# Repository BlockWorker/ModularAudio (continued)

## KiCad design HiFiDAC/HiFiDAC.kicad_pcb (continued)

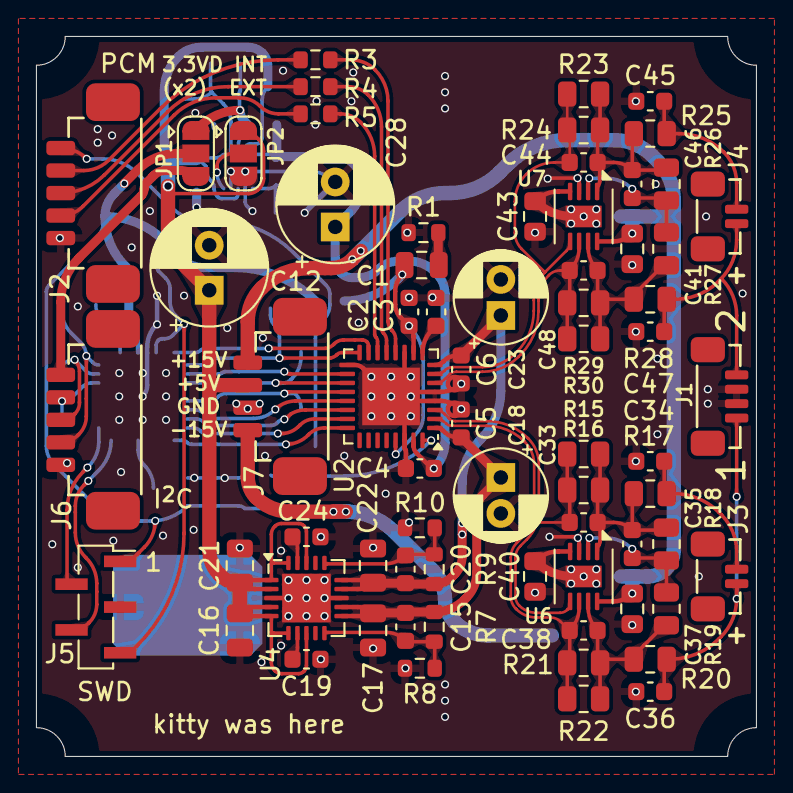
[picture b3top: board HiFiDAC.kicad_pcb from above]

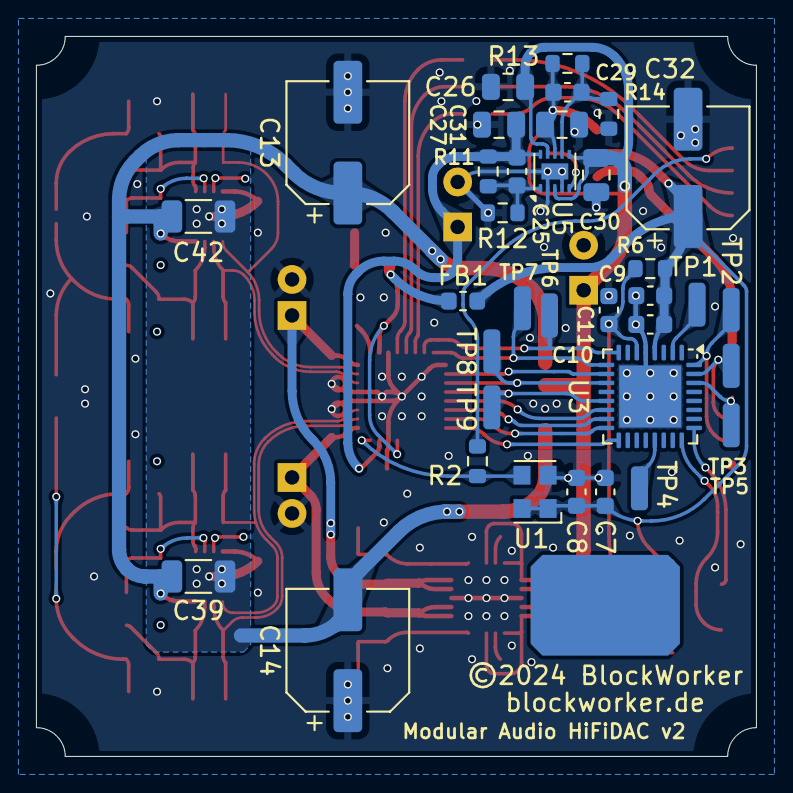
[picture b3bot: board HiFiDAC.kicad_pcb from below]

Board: 4 copper layers, 40.0 x 40.0 mm, 104 parts (35 on the bottom side), 59 nets.

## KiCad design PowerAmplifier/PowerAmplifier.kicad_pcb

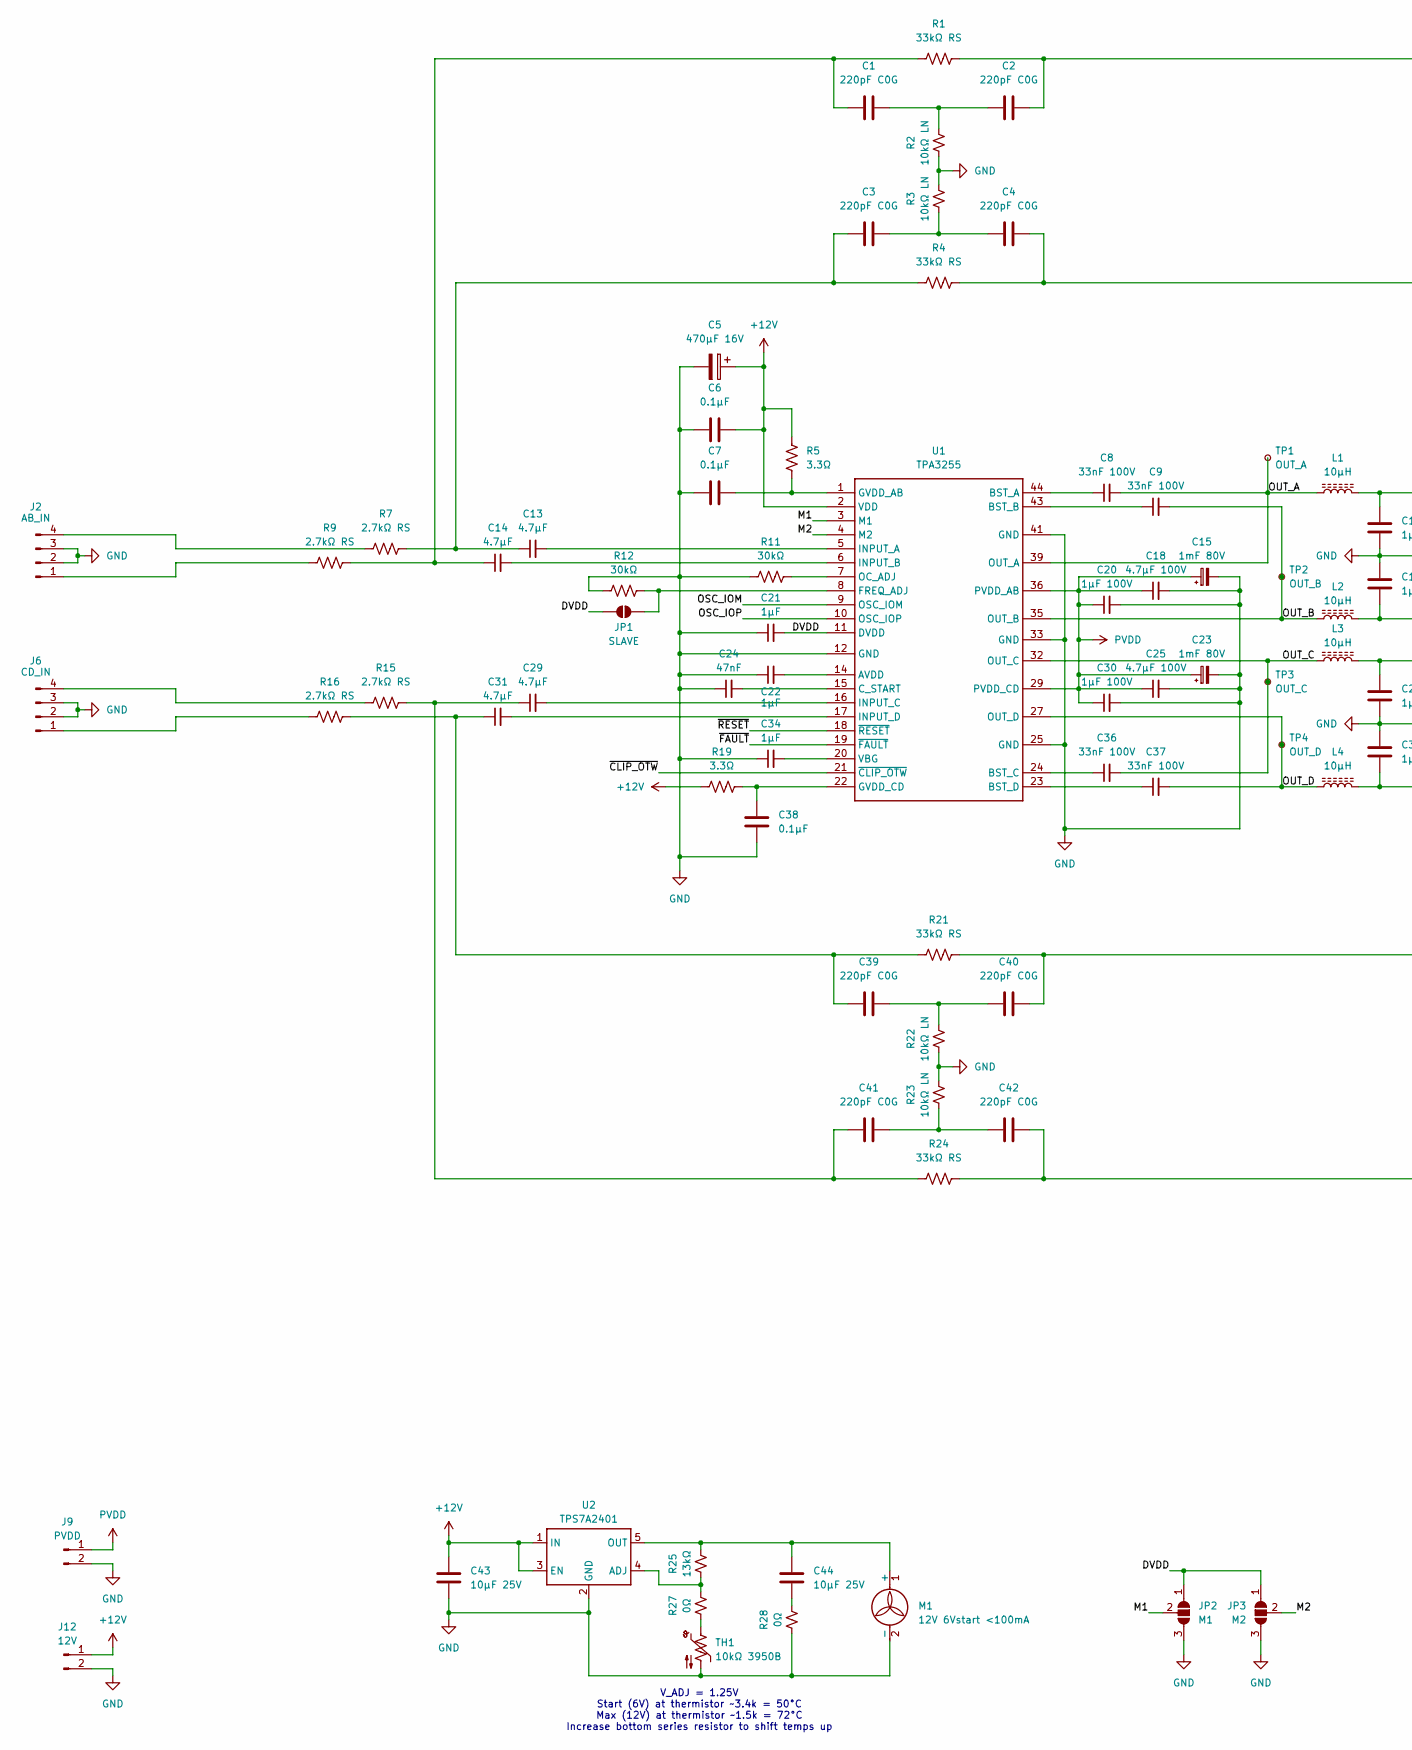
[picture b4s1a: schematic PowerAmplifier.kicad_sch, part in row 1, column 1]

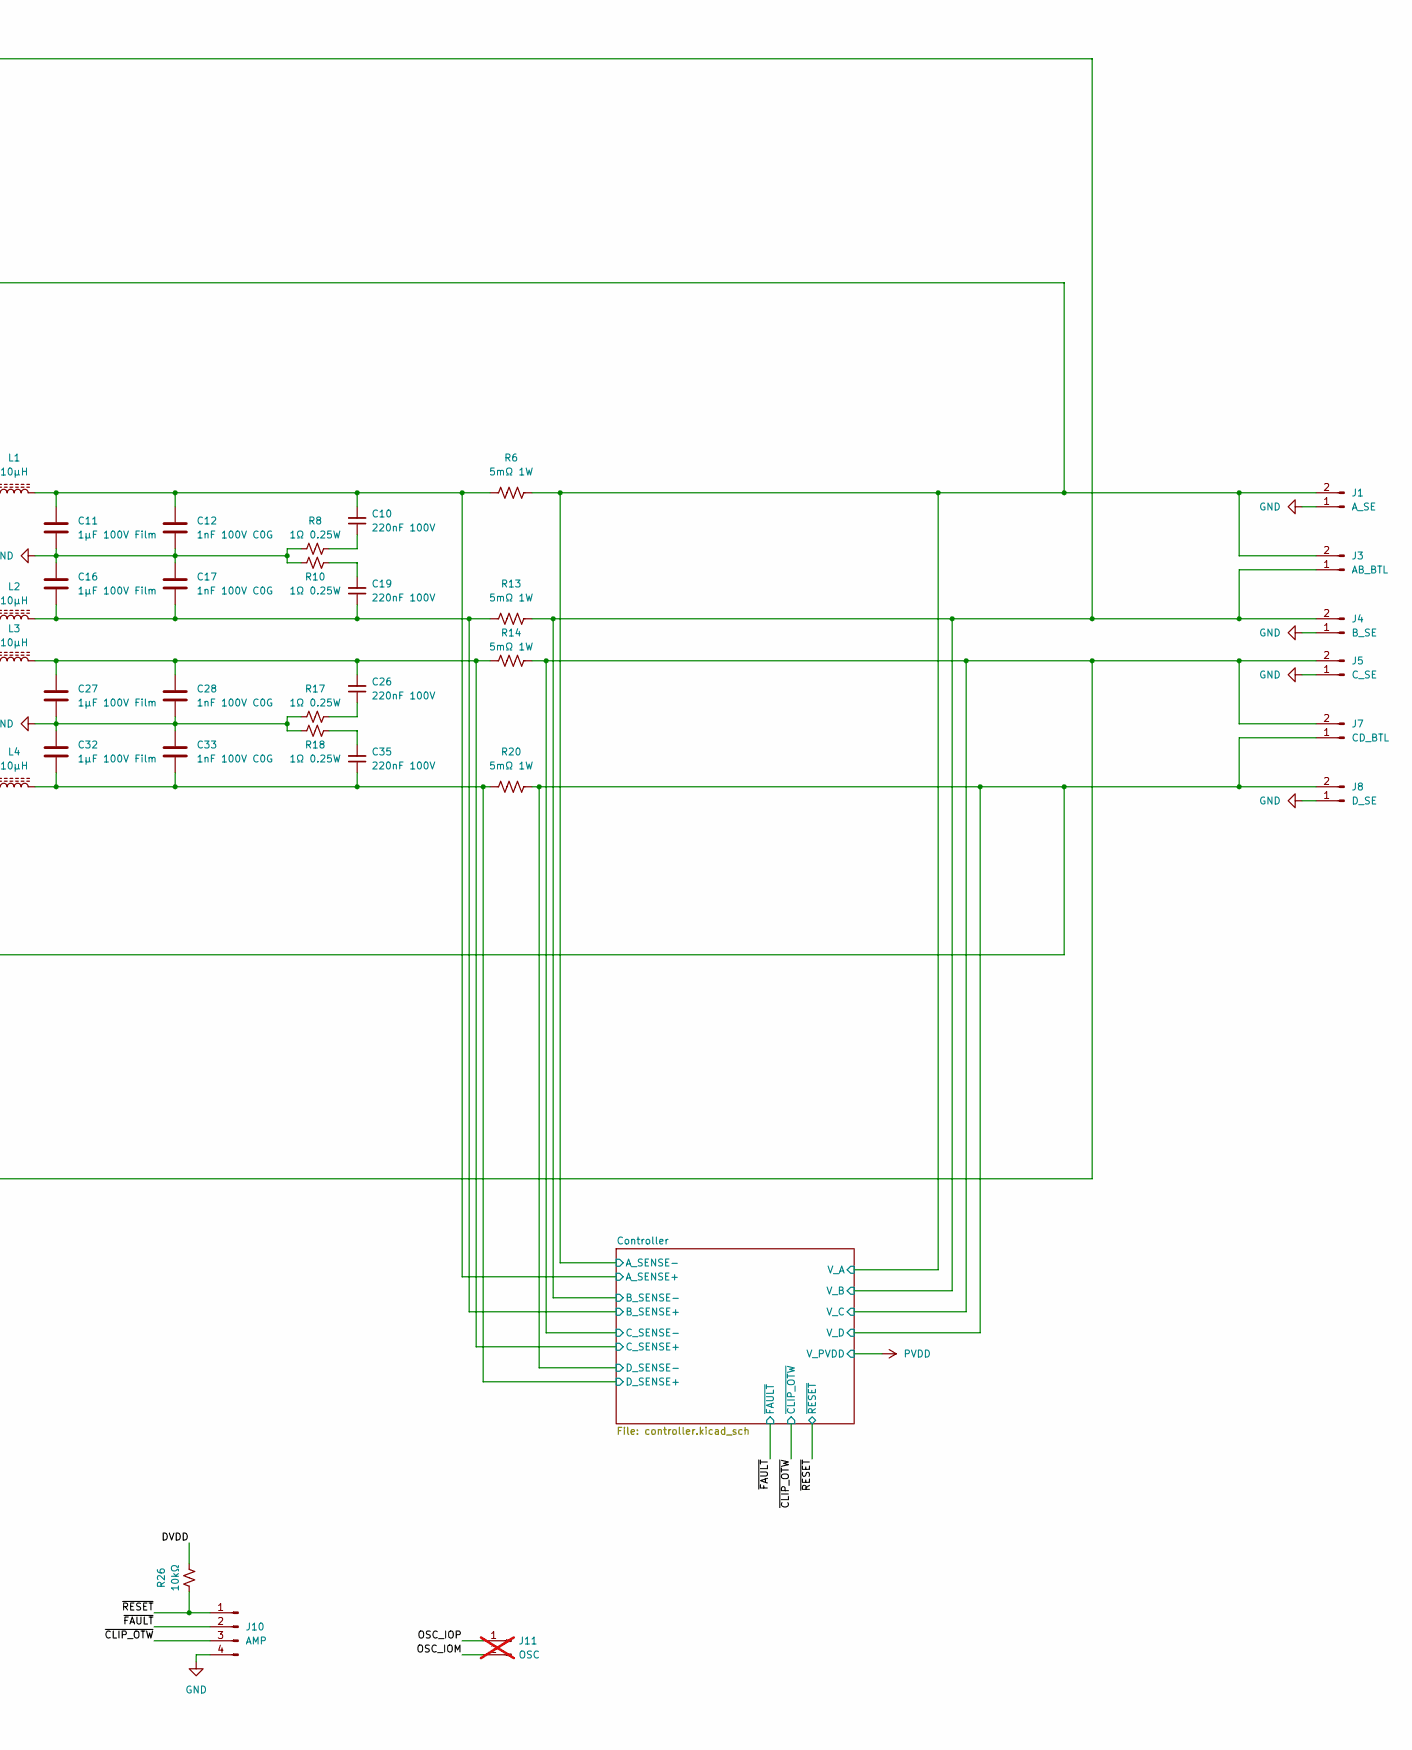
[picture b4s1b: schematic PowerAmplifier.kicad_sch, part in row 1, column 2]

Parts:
C1, C2, C3, C4, C39, C40, C41, C42: 220pF C0G; C_0603_1608Metric
C5: 470µF 16V; CP_Radial_D8.0mm_P3.50mm
C6, C7, C38: 0.1µF; C_0603_1608Metric
C8, C9, C36, C37: 33nF 100V; C_0603_1608Metric
C10, C19, C26, C35: 220nF 100V; C_0805_2012Metric
C11, C16, C27, C32: 1µF 100V Film; C_Rect_L7.0mm_W6.0mm_P5.00mm
C12, C17, C28, C33: 1nF 100V C0G; C_0603_1608Metric
C13, C14, C29, C31: 4.7µF; C_Rect_L7.2mm_W7.2mm_P5.00mm_FKS2_FKP2_MKS2_MKP2
C15, C23: 1mF 80V; CP_Radial_D16.0mm_P7.50mm
C18, C25: 4.7µF 100V; C_1206_3216Metric
C20, C30: 1µF 100V; C_1206_3216Metric
C21, C22, C34: 1µF; C_0603_1608Metric
C24: 47nF; C_0603_1608Metric
C43, C44: 10µF 25V; C_0805_2012Metric
J1: A_SE; TE_MATE-N-LOK_1-770872-x_1x02_P4.14mm_Vertical
J2: AB_IN; Amphenol_MINITEK_0.8_4P_V_BoardEdge
J3: AB_BTL; TE_MATE-N-LOK_1-770872-x_1x02_P4.14mm_Vertical
J4: B_SE; TE_MATE-N-LOK_1-770872-x_1x02_P4.14mm_Vertical
J5: C_SE; TE_MATE-N-LOK_1-770872-x_1x02_P4.14mm_Vertical
J6: CD_IN; Amphenol_MINITEK_0.8_4P_V_BoardEdge
J7: CD_BTL; TE_MATE-N-LOK_1-770872-x_1x02_P4.14mm_Vertical
J8: D_SE; TE_MATE-N-LOK_1-770872-x_1x02_P4.14mm_Vertical
J9: PVDD; TE_644749-2
J10: AMP; Amphenol_MINITEK_0.8_4P_V_BoardEdge
J11: OSC; Amphenol_MINITEK_0.8_2P_V; not fitted
J12: 12V; Amphenol_MINITEK_0.8_2P_V_BoardEdge
JP1: SLAVE; SolderJumper-2_P1.3mm_Open_RoundedPad1.0x1.5mm
JP2: M1; SolderJumper-3_P1.3mm_Open_RoundedPad1.0x1.5mm
JP3: M2; SolderJumper-3_P1.3mm_Open_RoundedPad1.0x1.5mm
L1, L2, L3, L4: 10µH; L_ICE_1D17A
M1: 12V 6Vstart <100mA; Amphenol_MINITEK_0.8_2P_V
R1, R4, R21, R24: 33kΩ RS; R_0805_2012Metric
R2, R3, R22, R23: 10kΩ LN; R_0603_1608Metric
R5, R19: 3.3Ω; R_0805_2012Metric
R6, R13, R14, R20: 5mΩ 1W; R_0612_1632Metric
R7, R9, R15, R16: 2.7kΩ RS; R_0805_2012Metric
R8, R10, R17, R18: 1Ω 0.25W; R_0603_1608Metric
R11, R12: 30kΩ; R_0603_1608Metric
R25: 13kΩ; R_0603_1608Metric
R26: 10kΩ; R_0603_1608Metric
R27, R28: 0Ω; R_0603_1608Metric
TH1: 10kΩ 3950B; R_0603_1608Metric
TP1: OUT_A; TP_0603_1608Metric_Fused
TP2: OUT_B; TP_0603_1608Metric_Fused
TP3: OUT_C; TP_0603_1608Metric_Fused
TP4: OUT_D; TP_0603_1608Metric_Fused
U1: TPA3255; HTSSOP-44_6.1x14mm_P0.635mm
U2: TPS7A2401; SOT-23-5

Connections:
+12V: C5.1, C6.1, C43.1, J12.1, R5.2, R19.1, U1.2 (VDD), U2.1 (IN), U2.3 (EN); also elsewhere on the board
/Controller/A_SENSE+: C10.2, C11.1, C12.1, L1.2, R6.2; also elsewhere on the board
/Controller/A_SENSE-: C4.1, J1.2, J3.2, R4.1, R6.1; also elsewhere on the board
/Controller/B_SENSE+: C16.2, C17.2, C19.1, L2.2, R13.2; also elsewhere on the board
/Controller/B_SENSE-: C2.1, J3.1, J4.2, R1.1, R13.1; also elsewhere on the board
/Controller/C_SENSE+: C26.2, C27.1, C28.1, L3.2, R14.2; also elsewhere on the board
/Controller/C_SENSE-: C42.1, J5.2, J7.2, R14.1, R24.1; also elsewhere on the board
/Controller/D_SENSE+: C32.2, C33.2, C35.1, L4.2, R20.2; also elsewhere on the board
/Controller/D_SENSE-: C40.1, J7.1, J8.2, R20.1, R21.1; also elsewhere on the board
/DVDD: C21.2, JP1.1 (A), JP2.1 (A), JP3.1 (A), R26.1, U1.11 (DVDD)
/M1: JP2.2 (C), U1.3 (M1)
/M2: JP3.2 (C), U1.4 (M2)
/OSC_IOM: J11.2, U1.9 (OSC_IOM)
/OSC_IOP: J11.1, U1.10 (OSC_IOP)
/OUT_A: C8.2, L1.1, TP1.1, U1.39 (OUT_A), U1.40 (OUT_A)
/OUT_B: C9.2, L2.1, TP2.1, U1.35 (OUT_B)
/OUT_C: C36.2, L3.1, TP3.1, U1.32 (OUT_C)
/OUT_D: C37.2, L4.1, TP4.1, U1.27 (OUT_D), U1.28 (OUT_D)
/~CLIP_OTW: J10.3, U1.21 (~CLIP_OTW); also elsewhere on the board
/~FAULT: J10.2, U1.19 (~FAULT); also elsewhere on the board
/~RESET: J10.1, R26.2, U1.18 (~RESET); also elsewhere on the board
GND: C5.2, C6.2, C7.2, C11.2, C12.2, C15.2, C16.1, C17.1, C18.2, C20.2, C21.1, C22.1, C23.2, C24.1, C25.2, C27.2, C28.2, C30.2, C32.1, C33.1, C34.1, C38.2, C43.2, J1.1, J2.2, J2.3, J4.1, J5.1, J6.2, J6.3, J8.1, J9.2, J10.4, J12.2, JP2.3 (B), JP3.3 (B), M1.2 (-), R2.2, R3.1, R8.2, R10.2, R11.2, R12.2, R17.2, R18.2, R22.2, R23.1, R28.2, TH1.2, U1.12 (GND), U1.13 (GND), U1.25 (GND), U1.26 (GND), U1.33 (GND), U1.34 (GND), U1.41 (GND), U1.42 (GND), U2.2 (GND); also elsewhere on the board
unnamed: C1.1, C2.2, R2.1
unnamed: C1.2, C14.1, R1.2, R9.1
unnamed: C3.1, C4.2, R3.2
unnamed: C10.1, R8.1
unnamed: C3.2, C13.1, R4.2, R7.1
unnamed: C19.2, R10.1
unnamed: C26.1, R17.1
unnamed: C29.1, C41.2, R15.1, R24.2
unnamed: C31.1, C39.2, R16.1, R21.2
unnamed: C35.2, R18.1
unnamed: C39.1, C40.2, R22.1
unnamed: C41.1, C42.2, R23.2
unnamed: C44.2, R28.1
unnamed: J2.1, R9.2
unnamed: J2.4, R7.2
unnamed: J6.1, R16.2
unnamed: J6.4, R15.2
unnamed: JP1.2 (B), R12.1, U1.8 (FREQ_ADJ)
unnamed: C44.1, M1.1 (+), R25.1, U2.5 (OUT)
unnamed: R27.2, TH1.1
unnamed: C22.2, U1.14 (AVDD)
unnamed: C8.1, U1.44 (BST_A)
unnamed: C9.1, U1.43 (BST_B)
unnamed: C36.1, U1.24 (BST_C)
unnamed: C37.1, U1.23 (BST_D)
unnamed: C24.2, U1.15 (C_START)
unnamed: C7.1, R5.1, U1.1 (GVDD_AB)
unnamed: C38.1, R19.2, U1.22 (GVDD_CD)
unnamed: C13.2, U1.5 (INPUT_A)
unnamed: C14.2, U1.6 (INPUT_B)
unnamed: C29.2, U1.16 (INPUT_C)
unnamed: C31.2, U1.17 (INPUT_D)
unnamed: R11.1, U1.7 (OC_ADJ)
unnamed: C34.2, U1.20 (VBG)
unnamed: R25.2, R27.1, U2.4 (ADJ)
PVDD: C15.1, C18.1, C20.1, C23.1, C25.1, C30.1, J9.1, U1.29 (PVDD_CD), U1.30 (PVDD_CD), U1.31 (PVDD_CD), U1.36 (PVDD_AB), U1.37 (PVDD_AB), U1.38 (PVDD_AB); also elsewhere on the board

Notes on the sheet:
V_ADJ = 1.25V Start (6V) at thermistor ~3.4k = 50°C Max (12V) at thermistor ~1.5k = 72°C Increase bottom series resistor to shift temps up

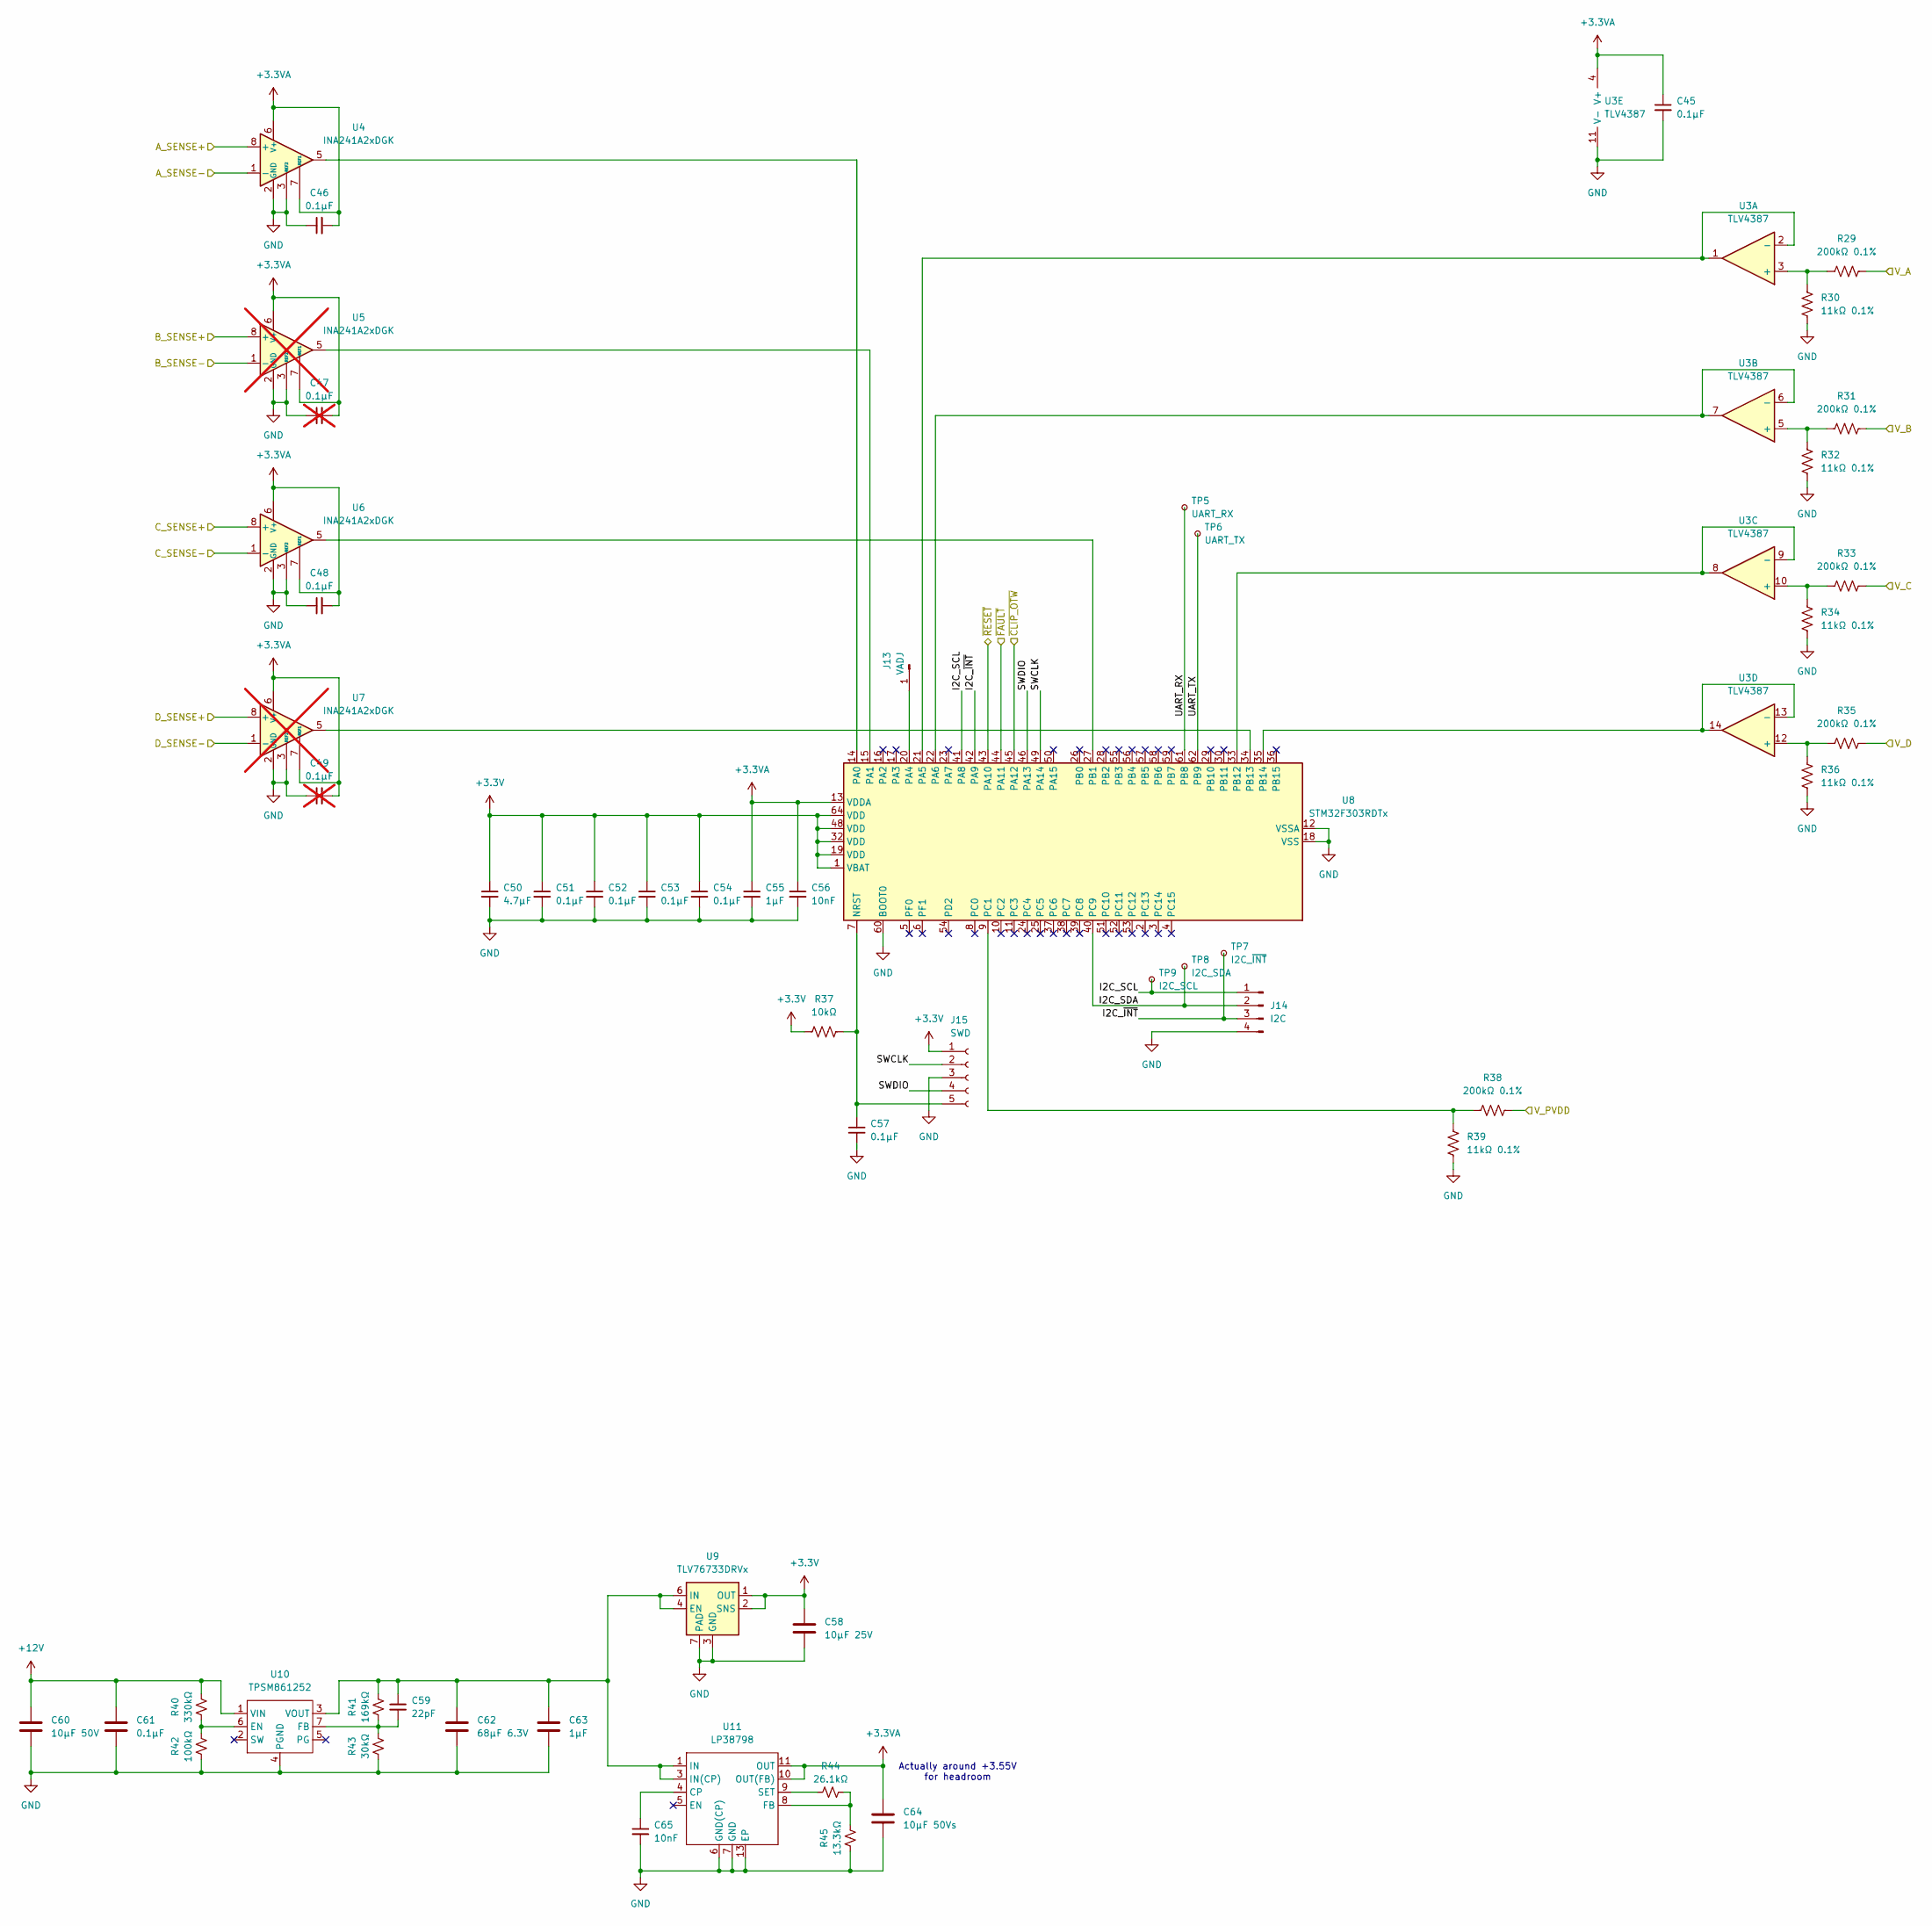
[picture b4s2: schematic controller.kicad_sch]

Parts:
C45, C46, C48, C51, C52, C53, C54, C57, C61: 0.1µF; C_0603_1608Metric
C47, C49: 0.1µF; C_0603_1608Metric; not fitted
C50: 4.7µF; C_0603_1608Metric
C55, C63: 1µF; C_0603_1608Metric
C56, C65: 10nF; C_0603_1608Metric
C58: 10µF 25V; C_0805_2012Metric
C59: 22pF; C_0603_1608Metric
C60: 10µF 50V; C_1206_3216Metric
C62: 68µF 6.3V; C_1206_3216Metric
C64: 10µF 50Vs; C_0805_2012Metric
J13: VADJ; PinHeader_1x01_P2.54mm_Vertical
J14: I2C; Amphenol_MINITEK_0.8_4P_V_BoardEdge
J15: SWD; PinSocket_1x05_P1.27mm_Vertical_SMD_Pin1Right
R29, R31, R33, R35, R38: 200kΩ 0.1%; R_0603_1608Metric
R30, R32, R34, R36, R39: 11kΩ 0.1%; R_0603_1608Metric
R37: 10kΩ; R_0603_1608Metric
R40: 330kΩ; R_0603_1608Metric
R41: 169kΩ; R_0603_1608Metric
R42: 100kΩ; R_0603_1608Metric
R43: 30kΩ; R_0603_1608Metric
R44: 26.1kΩ; R_0603_1608Metric
R45: 13.3kΩ; R_0603_1608Metric
TP5: UART_RX; TP_0603_1608Metric_Fused
TP6: UART_TX; TP_0603_1608Metric_Fused
TP7: I2C_~{INT}; TP_0603_1608Metric_Fused
TP8: I2C_SDA; TP_0603_1608Metric_Fused
TP9: I2C_SCL; TP_0603_1608Metric_Fused
U3: TLV4387; TSSOP-14_4.4x5mm_P0.65mm
U4, U6: INA241A2xDGK; VSSOP-8_3x3mm_P0.65mm
U5, U7: INA241A2xDGK; VSSOP-8_3x3mm_P0.65mm; not fitted
U8: STM32F303RDTx; LQFP-64_10x10mm_P0.5mm
U9: TLV76733DRVx; WSON-6-1EP_2x2mm_P0.65mm_EP1x1.6mm_LongerPads
U10: TPSM861252; TI_QFN-FCMOD
U11: LP38798; WSON-12-1EP_4x4mm_P0.5mm_EP2.6x3mm

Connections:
+3.3V: C50.1, C51.1, C52.1, C53.1, C54.1, C58.1, J15.1, R37.1, U8.1 (VBAT), U8.19 (VDD), U8.32 (VDD), U8.48 (VDD), U8.64 (VDD), U9.1 (OUT), U9.2 (SNS)
+3.3VA: C45.1, C46.2, C47.2, C48.2, C49.2, C55.1, C56.1, C64.1, U3.4 (V+), U4.6 (V+), U4.7 (REF1), U5.6 (V+), U5.7 (REF1), U6.6 (V+), U6.7 (REF1), U7.6 (V+), U7.7 (REF1), U8.13 (VDDA), U11.10 (OUT(FB)), U11.11 (OUT), U11.12 (OUT)
+12V: C60.1, C61.1, R40.1, U10.1 (VIN); also elsewhere on the board
/Controller/A_SENSE+: U4.8 (+); also elsewhere on the board
/Controller/A_SENSE-: R29.1, U4.1 (-); also elsewhere on the board
/Controller/B_SENSE+: U5.8 (+); also elsewhere on the board
/Controller/B_SENSE-: R31.1, U5.1 (-); also elsewhere on the board
/Controller/C_SENSE+: U6.8 (+); also elsewhere on the board
/Controller/C_SENSE-: R33.1, U6.1 (-); also elsewhere on the board
/Controller/D_SENSE+: U7.8 (+); also elsewhere on the board
/Controller/D_SENSE-: R35.1, U7.1 (-); also elsewhere on the board
/Controller/I2C_SCL: J14.1, TP9.1, U8.41 (PA8)
/Controller/I2C_SDA: J14.2, TP8.1, U8.40 (PC9)
/Controller/I2C_~INT: J14.3, TP7.1, U8.42 (PA9)
/Controller/SWCLK: J15.2, U8.49 (PA14)
/Controller/SWDIO: J15.4, U8.46 (PA13)
/Controller/UART_RX: TP5.1, U8.61 (PB8)
/Controller/UART_TX: TP6.1, U8.62 (PB9)
/~CLIP_OTW: U8.45 (PA12); also elsewhere on the board
/~FAULT: U8.44 (PA11); also elsewhere on the board
/~RESET: U8.43 (PA10); also elsewhere on the board
GND: C45.2, C46.1, C47.1, C48.1, C49.1, C50.2, C51.2, C52.2, C53.2, C54.2, C55.2, C56.2, C57.2, C58.2, C60.2, C61.2, C62.2, C63.2, C64.2, C65.2, J14.4, J15.3, R30.1, R32.1, R34.1, R36.1, R39.1, R42.2, R43.2, R45.2, U3.11 (V-), U4.2 (GND), U4.3 (REF2), U4.4 (GND), U5.2 (GND), U5.3 (REF2), U5.4 (GND), U6.2 (GND), U6.3 (REF2), U6.4 (GND), U7.2 (GND), U7.3 (REF2), U7.4 (GND), U8.12 (VSSA), U8.18 (VSS), U8.31 (VSS), U8.47 (VSS), U8.60 (BOOT0), U8.63 (VSS), U9.3 (GND), U9.5 (GND), U9.7 (PAD), U10.4 (PGND), U11.6 (GND(CP)), U11.7 (GND), U11.13 (EP); also elsewhere on the board
unnamed: J13.1, U8.20 (PA4)
unnamed: C57.1, J15.5, R37.2, U8.7 (NRST)
unnamed: R29.2, R30.2, U3.3 (+)
unnamed: U3.1, U3.2 (-), U8.21 (PA5)
unnamed: R31.2, R32.2, U3.5 (+)
unnamed: U3.6 (-), U3.7, U8.22 (PA6)
unnamed: R33.2, R34.2, U3.10 (+)
unnamed: U3.8, U3.9 (-), U8.33 (PB12)
unnamed: R35.2, R36.2, U3.12 (+)
unnamed: U3.13 (-), U3.14, U8.35 (PB14)
unnamed: U4.5, U8.14 (PA0)
unnamed: U5.5, U8.15 (PA1)
unnamed: U6.5, U8.27 (PB1)
unnamed: U7.5, U8.34 (PB13)
unnamed: R38.2, R39.2, U8.9 (PC1)
unnamed: R40.2, R42.1, U10.6 (EN)
unnamed: C59.2, R41.2, R43.1, U10.7 (FB)
unnamed: C59.1, C62.1, C63.1, R41.1, U9.4 (EN), U9.6 (IN), U10.3 (VOUT), U11.1 (IN), U11.2 (IN), U11.3 (IN(CP))
unnamed: C65.1, U11.4 (CP)
unnamed: R44.1, R45.1, U11.8 (FB)
unnamed: R44.2, U11.9 (SET)
PVDD: R38.1; also elsewhere on the board

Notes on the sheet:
Actually around +3.55V for headroom

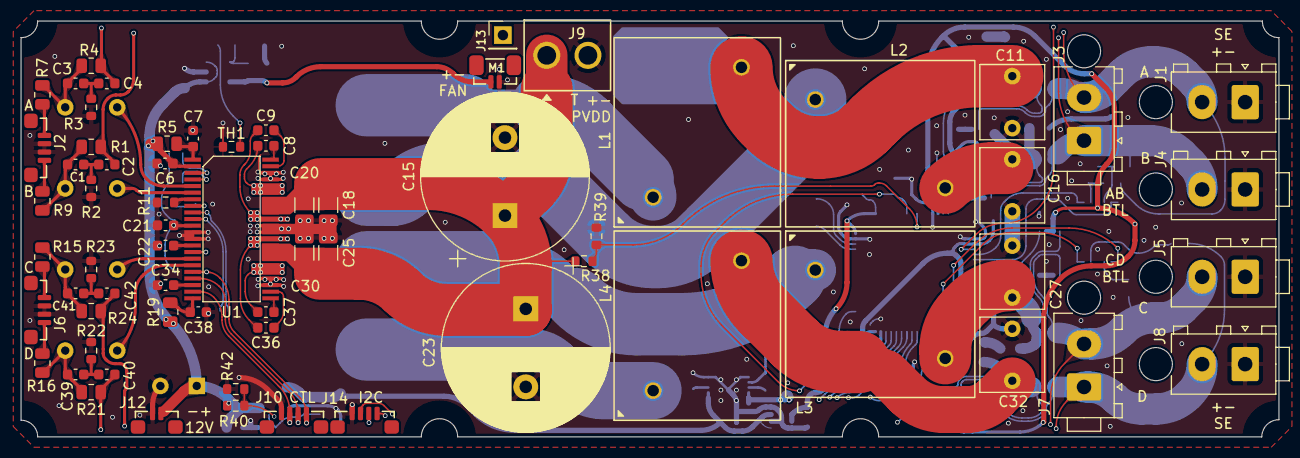
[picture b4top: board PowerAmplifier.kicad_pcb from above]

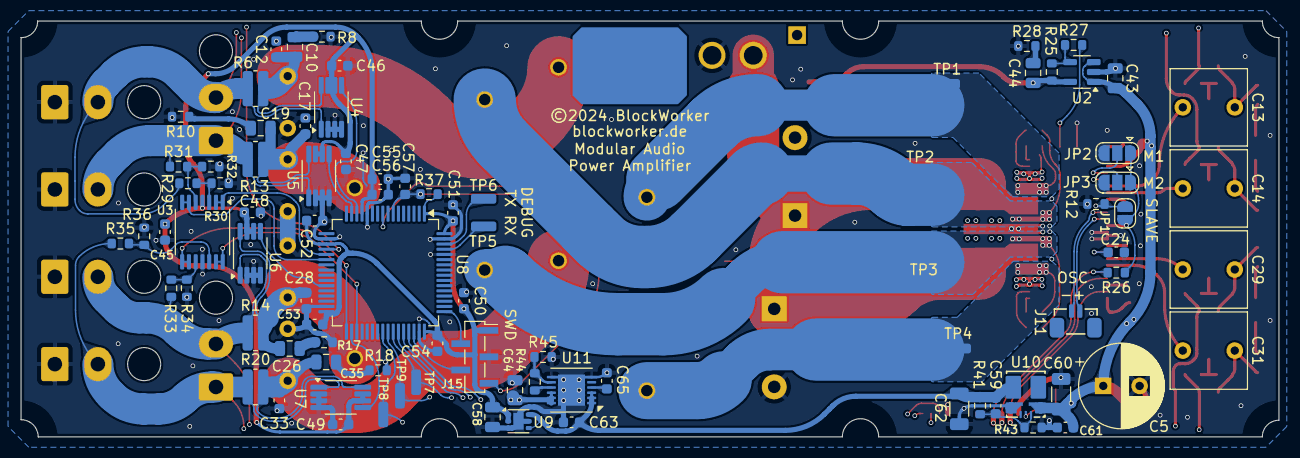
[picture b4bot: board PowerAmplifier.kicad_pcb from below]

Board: 4 copper layers, 121.0 x 40.0 mm, 155 parts (87 on the bottom side), 88 nets.

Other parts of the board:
HS1: ATS-xPX035035035_NoMounts
